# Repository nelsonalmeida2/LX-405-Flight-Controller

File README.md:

<div align="center">

# 🚁 LX-405 Flight Controller

<div align="center">
  
</div>

**A robust, Open Source FPV Flight Controller designed by a Computer Engineering student.**

</div>

---

## 🎯 Motivation & Philosophy

> *"In the modern era, Artificial Intelligence combined with human effort makes the impossible, inevitable."*

The **LX-405** project was born from a realization: as a Computer Engineering student entering the high-speed world of FPV, I found that too many flight controllers on the market suffer from electrical noise, weak regulators, and fragility under 6S voltage spikes.

My goal is to prove that **modern engineering is boundary-less**. Even though my degree is not strictly focused on electronics, the foundational skills acquired in my academic path—combined with a self-taught mindset and the leverage of **Large Language Models (LLMs)** as advanced design assistants—allow for the creation of professional-grade hardware.

This project demonstrates that with the right theoretical foundations and modern AI tools, it is possible to design a Flight Controller that is **more robust, cleaner, and potentially more cost-effective** at scale.

### 📐 Design Strategy: Modular & Hierarchical
Unlike typical hobbyist "flat" schematics, the LX-405 follows a strict **Hierarchical Design** approach.
Applying the software engineering principle of **Modularity** (Separation of Concerns), the hardware is divided into distinct hierarchical subsystems:
* **Power Management:** Encapsulates the voltage regulation logic (5V, 9V, 3.3V) with clean "Power Flags" logic.
* **MCU Core:** Contains the processor logic, clock, signaling, and boot configuration.
* **System Peripherals:** Groups active sensors (Gyro, Baro), OSD video processing logic, **Blackbox Logging**, and user feedback systems (LEDs/Buzzer).
* **Connectors IO:** Isolates physical interface definitions (plugs/pads) from logical connections to prevent routing conflicts.

### 🎓 Academic Foundations
This design applies core concepts from my Computer Engineering curriculum at **Universidade Lusófona**:
* **Digital Systems:** Logic gates and boolean algebra applied to circuit switching.
* **Computer Architecture:** Understanding CPU data paths, buses, registers, and instruction execution.
* **Advanced Computer Architectures:** Knowledge of processor constraints, memory hierarchy (cache), and hardware-software interaction.
* **Fundamentals of Physics:** Electromagnetism, electric fields, circuit analysis, and DC power dynamics.

---

## ⚡ Technical Specifications

### 🧠 Core System (Schematic Completed)
* **MCU:** STM32F405RGT6 (168MHz, 1MB Flash).
* **Clock:** 8MHz HSE Crystal Oscillator with 22pF load caps for precision timing.
* **Signal Integrity:** Dedicated LC Filter (Ferrite Bead + Caps) for **VDDA** analog noise suppression.
* **Safety:** Hardware-implemented Watchdog (NRST) and Bootloader (BOOT0) physical controls.

### 📡 Connectivity & Protocols
* **USB Interface:** Modern **USB-C** connector with dedicated ESD protection lines for firmware updates and Betaflight configuration.
* **Motor Protocols:**
    * 4x DSHOT Outputs (Timer-mapped for DMA collision avoidance).
    * **Redundant ESC Pads:** Parallel solder pads for motor signals, allowing field repairs if the main JST connector breaks.
* **Communication Ports:** 5x UARTs fully mapped for versatility:
    * **UART 1:** RC Link (ELRS / Crossfire).
    * **UART 2:** GPS / General Purpose.
    * **UART 3:** **Video Link** (SmartAudio for Analog **OR** MSP for DJI O3/HDZero).
    * **UART 4:** ESC Telemetry (Sensor Input).
    * **UART 6:** Peripheral Expansion (Bluetooth, Lidar, Secondary GPS).
    * *(Note: UART 5 was replaced by the High-Speed SDIO Bus).*
* **Video System (Hybrid):**
    * Dedicated **"Hybrid Power Pad"** offering both **5V** (Analog) and **9V** (High Power Digital) options for the VTX.
    * **Analog OSD:** **MAX7456** (or **AT7456E**) on SPI2 with dedicated video filtering.
* **Sensor Bus:** Dedicated SPI1 (High-Speed Gyro) and I2C1 (Barometer).

### 🛡️ On-Board Sensors & Peripherals
* **IMU (Gyroscope):** **BMI270** connected via Low-Noise **SPI1**.
    * Features hardware **EXTI Interrupt** (PC4) for ultra-low latency loop synchronization.
* **Barometer:** **DPS310** connected via **I2C1** for high-precision altitude hold.
* **Blackbox Logging:** **MicroSD Card Slot** via **4-bit SDIO** Interface.
    * Superior performance compared to SPI logging, enabling high-frequency data recording without CPU bottlenecks.
* **User Feedback:**
    * **Status LEDs:** Dedicated **LED_POWER** (Red) and **LED_STATUS** (Blue) for instant system diagnostics.
    * **Buzzer Driver:** Integrated active buzzer circuit for alarms and "turtle mode" feedback.

### 🔋 Power Plant (Tri-Rail Architecture)
A hierarchical power distribution system designed to minimize noise coupling and maximize versatility:

| Rail | Regulator | Specs | Application |
| :--- | :--- | :--- | :--- |
| **Input** | XT60 Direct | **3S-6S (10V - 25.2V)** | Wide-range input for Cinematic (6S) & Freestyle (4S) |
| **9V Rail** | TPS54302 | 3A Buck | **Hybrid Video Ready:** Supports DJI O3/Vista & Analog VTX |
| **5V Rail** | TPS54302 | 3A Buck | GPS, ELRS Receiver, Buzzer, OSD Chip |
| **3.3V Rail** | AP2112K | 500mA LDO | **Ultra-Low Noise** for MCU, Gyro, Baro & Blackbox |

---

## 📂 Repository Structure

```text
LX-405-Flight-Controller/
├── 📂 Hardware/          # KiCad Project Files (Schematics, PCB & Symbols)
├── 📂 Schematic/         # PDF Exports for easy viewing
├── 📂 Docs/              # Datasheets and Engineering Notes
├── 📄 LICENSE            # MIT License details
└── 📄 README.md          # Documentation
```
## 🛠 Development Roadmap

### Phase 1: Schematic Design 🔌

- [x] **Power Management**
    - [x] Input Stage: TVS protection and bulk capacitance (3S–6S filtering)
    - [x] 5V Regulator: Synchronous buck (TPS54302)
    - [x] 9V Regulator: High-current buck (TPS54302) for HD video
    - [x] 3.3V Regulator: Low-noise LDO (AP2112K) for sensors

- [x] **MCU Core**
    - [x] STM32F405RGT6: Symbol integration and pin definition
    - [x] Power decoupling & analog filtering (VDDA)
    - [x] Clock system: 8 MHz HSE crystal
    - [x] I/O architecture: Full UART / SPI / I2C mapping validation

- [x] **System Peripherals**
    - [x] Gyroscope (BMI270) via SPI1
    - [x] Barometer (DPS310) via I2C with address fix
    - [x] Blackbox: High-speed SDIO MicroSD slot implementation
    - [x] On-screen display (MAX7456 / AT7456E) via SPI2
    - [x] Visual / Audio: Status LEDs & buzzer circuit implemented

- [x] **Connectors & I/O**
    - [x] USB-C interface (data lines & ESD protection logic)
    - [x] ESC connector (standard pinout with telemetry)
    - [x] ESC redundancy: Parallel solder pads for emergency field repairs
    - [x] Hybrid VTX connector (selectable 5V / 9V)

- [x] **Design Validation**
    - [x] Electrical Rules Check (ERC): **PASSED with 0 errors**
    - [x] Schematic design finalized (**v0.6**)

### Phase 2: PCB Layout 📐

- [x] **Physical Implementation**
    - [x] Assign footprints (associating symbols with physical dimensions)
    - [x] Stackup definition (4-layer)
    - [x] Component placement (Optimized for noise reduction & assembly)
    - [x] Silkscreen & Labeling (User-friendly pin identification)
    - [ ] Routing (Traces & Ground Planes)
    - [ ] DRC (Design Rules Check) & Fabrication Output (Gerbers)

---

## 📜 License

This project is licensed under the **MIT License** — see the `LICENSE` file for details.

You are free to use, modify, and distribute this hardware design for private or commercial use, provided you include the original copyright notice.

As an **Open Source Hardware** project, contributions and forks are welcome.

---

<div align="center">

**Designed in Lisbon, Portugal 🇵🇹**  
Powered by Engineering Fundamentals & AI

</div>

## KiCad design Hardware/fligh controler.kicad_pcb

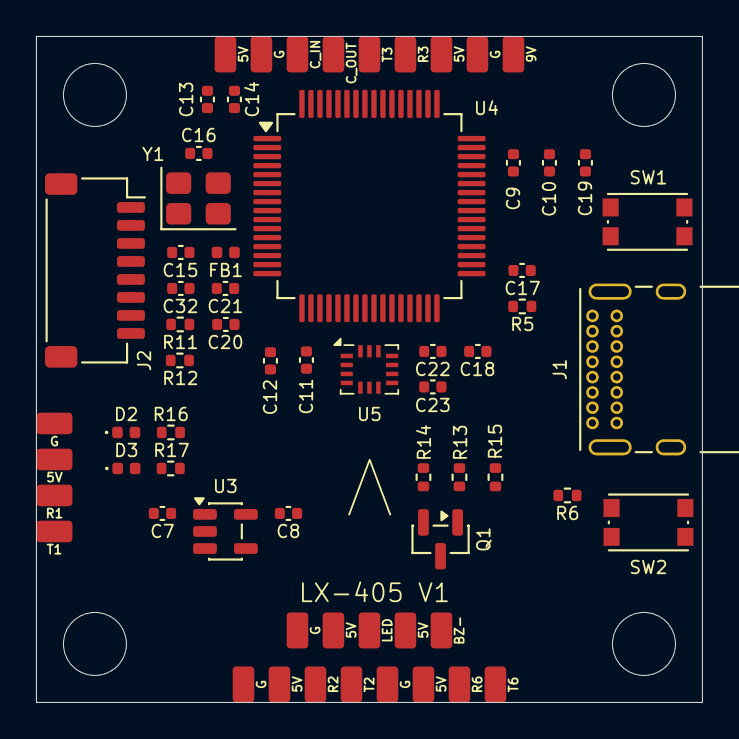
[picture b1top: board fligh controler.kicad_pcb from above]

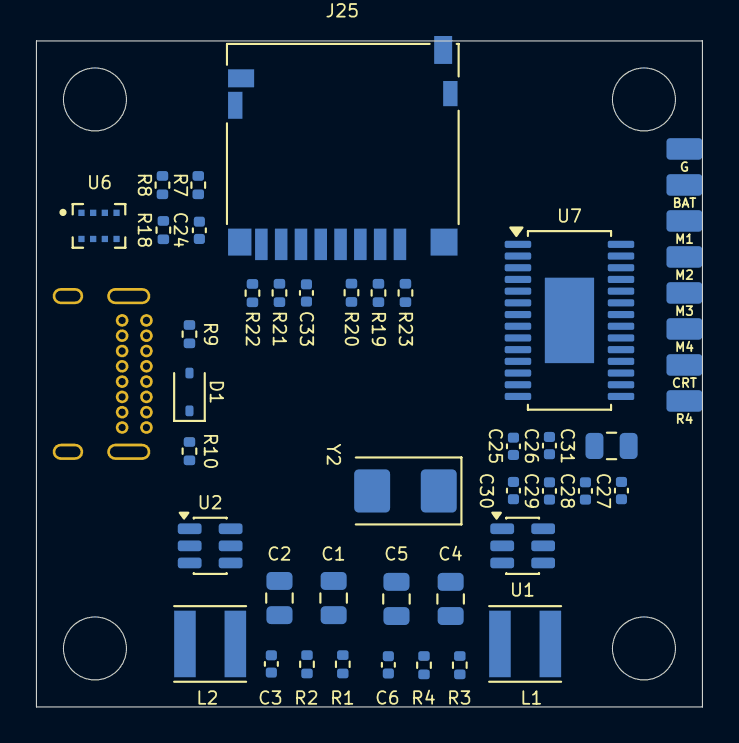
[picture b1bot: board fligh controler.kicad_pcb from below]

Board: 2 copper layers, 37.0 x 37.0 mm, 111 parts (46 on the bottom side), 70 nets, no tracks yet.

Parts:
5V, 5V#2, 5V#3, 5V#4, 5V#5, 5V#6, 5V#7: +5V; Pad_TestPoint_Retangular
9V: +9V; Pad_TestPoint_Retangular
BAT: BAT+; Pad_TestPoint_Retangular
BZ-: BUZZER-; Pad_TestPoint_Retangular
C1, C4: 10uF 50V; C_0805_2012Metric
C2: 22uF 25V; C_0805_2012Metric
C3, C6: 0.1uF 50V; C_0402_1005Metric
C5: 22uF 10V; C_0805_2012Metric
C7, C8, C21: 1uF 16V; C_0402_1005Metric
C9, C10, C11, C12, C13, C17, C20, C22, C23, C24, C25, C26, C27, C30, C32, C33: 100nF 16V; C_0402_1005Metric
C14, C18, C19: 4.7uF 16V; C_0402_1005Metric
C15, C16, C28, C29: 22pF 16V; C_0402_1005Metric
C31: 47uF 16V; C_0805_2012Metric
CRT: CURRENT_SENSE; Pad_TestPoint_Retangular
C_IN: CAM_VIDEO_IN; Pad_TestPoint_Retangular
C_OUT: VTX_VIDEO_OUT; Pad_TestPoint_Retangular
D1: D_Schottky; D_SOD-323
D2: Red; LED_0402_1005Metric
D3: Blue; LED_0402_1005Metric
FB1: 100R @ 100MHz; L_0402_1005Metric
G: GND; Pad_TestPoint_Retangular
G#2, G#3, G#4, G#5, G#6, G#7: GND; Pad_TestPoint_Retangular
J1: USB_C_Receptacle_USB2.0_16P; USB_C_Receptacle_GCT_USB4085
J2: Conn_01x08; JST_SH_SM08B-SRSS-TB_1x08-1MP_P1.00mm_Horizontal
J25: Micro_SD_Card; microSD_HC_Hirose_DM3D-SF
L1, L2: 10uH 3A; L_Taiyo-Yuden_NR-40xx
LED: LED_STRIP; Pad_TestPoint_Retangular
M1: MOTOR_1; Pad_TestPoint_Retangular
M2: MOTOR_2; Pad_TestPoint_Retangular
M3: MOTOR_3; Pad_TestPoint_Retangular
M4: MOTOR_4; Pad_TestPoint_Retangular
Q1: 2N7002; SOT-23
R1: RX1; Pad_TestPoint_Retangular
R1#2, R3#2: 100k 1%; R_0402_1005Metric
R2: RX2; Pad_TestPoint_Retangular
R2#2: 7.15k 1%; R_0402_1005Metric
R3: RX3; Pad_TestPoint_Retangular
R4: RX4; Pad_TestPoint_Retangular
R4#2: 13.7k 1%; R_0402_1005Metric
R5, R6, R11, R14: 10k; R_0402_1005Metric
R6#2: RX6; Pad_TestPoint_Retangular
R7, R8, R18: 4.7k; R_0402_1005Metric
R9, R10: 5.1k; R_0402_1005Metric
R12, R13, R16: 1k; R_0402_1005Metric
R15, R17: 330Ω; R_0402_1005Metric
R19, R20, R21, R22, R23: 47k; R_0402_1005Metric
SW1, SW2: SW_Push; SW_Push_1P1T_NO_CK_KMR2
T1: TX1; Pad_TestPoint_Retangular
T2: TX2; Pad_TestPoint_Retangular
T3: TX3; Pad_TestPoint_Retangular
T6: TX6; Pad_TestPoint_Retangular
U1, U2: TPS54302; SOT-23-6
U3: AP2112K-3.3; SOT-23-5
U4: STM32F405RGT6; LQFP-64_10x10mm_P0.5mm
U5: BMI270; Bosch_LGA-14_3x2.5mm_P0.5mm
U6: DPS310
U7: MAX7456EUI_T; TSSOP-28-1EP_4.4x9.7mm_P0.65mm_EP2.74x4.75mm
Y1: Crystal_GND24; Crystal_SMD_3225-4Pin_3.2x2.5mm
Y2: Crystal; Crystal_SMD_5032-2Pin_5.0x3.2mm

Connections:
+3V3: C8.2, C9.1, C10.1, C11.1, C12.1, C13.1, C14.1, C22.2, C23.2, C24.1, FB1.2, J25.4 (VDD), R5.1, R7.1, R8.2, R16.1, R19.1, R20.1, R21.1, R22.1, R23.1, SW2.2, U3.5 (VOUT), U4.1 (VBAT), U4.19 (VDD), U4.32 (VDD), U4.48 (VDD), U4.64 (VDD), U5.5 (VDDIO), U5.8 (VDD), U6.2 (~CSB), U6.6 (VDDIO), U6.8 (VDD)
+5V: 5V.1, 5V#2.1, 5V#3.1, 5V#4.1, 5V#5.1, 5V#6.1, 5V#7.1, C5.2, C7.2, C25.1, C26.1, C27.1, D1.1 (K), L2.1, R3#2.2, U3.1 (VIN), U3.3 (EN), U7.3 (DVDD), U7.19 (~RESET), U7.21 (AVDD), U7.24 (PVDD)
+9V: 9V.1, C2.2, L1.1, R1#2.2
/Connectors_IO/BUZZER-: BZ-.1, Q1.3 (D)
/Connectors_IO/CAM_VIDEO_IN: C30.2, C_IN.1
/Connectors_IO/CURRENT_SENSE: CRT.1, J2.7, U4.9 (PC1)
/Connectors_IO/LED_STRIP: R15.1, U4.14 (PA0)
/Connectors_IO/MOTOR_1: J2.3, M1.1, U4.26 (PB0)
/Connectors_IO/MOTOR_2: J2.4, M2.1, U4.27 (PB1)
/Connectors_IO/MOTOR_3: J2.5, M3.1, U4.56 (PB4)
/Connectors_IO/MOTOR_4: J2.6, M4.1, U4.57 (PB5)
/Connectors_IO/RX1: R1.1, U4.42 (PA9)
/Connectors_IO/RX2: R2.1, U4.16 (PA2)
/Connectors_IO/RX3: R3.1, U4.29 (PB10)
/Connectors_IO/RX4: J2.8, R4.1, U4.15 (PA1)
/Connectors_IO/RX6: R6#2.1, U4.37 (PC6)
/Connectors_IO/TX1: T1.1, U4.43 (PA10)
/Connectors_IO/TX2: T2.1, U4.17 (PA3)
/Connectors_IO/TX3: T3.1, U4.30 (PB11)
/Connectors_IO/TX6: T6.1, U4.38 (PC7)
/Connectors_IO/USB_DM: J1.A7 (D-), J1.B7 (D-), U4.44 (PA11)
/Connectors_IO/USB_DP: J1.A6 (D+), J1.B6 (D+), U4.45 (PA12)
/Connectors_IO/VTX_VIDEO_OUT: C31.2, C_OUT.1
/MCU_Core/BUZZER_CTRL: R13.2, U4.2 (PC13)
/MCU_Core/GYRO_CS: U4.20 (PA4), U5.12 (CSB)
/MCU_Core/GYRO_EXTI: U4.24 (PC4), U5.4 (INT1)
/MCU_Core/I2C1_SCL: R8.1, U4.58 (PB6), U6.4 (SCK)
/MCU_Core/I2C1_SDA: R7.2, U4.59 (PB7), U6.3 (SDI)
/MCU_Core/LED_STATUS: R17.1, U4.25 (PC5)
/MCU_Core/OSD_CS: U4.33 (PB12), U7.8 (~CS)
/MCU_Core/SDIO_CK: J25.5 (CLK), U4.53 (PC12)
/MCU_Core/SDIO_CMD: J25.3 (CMD), R20.2, U4.54 (PD2)
/MCU_Core/SDIO_D0: J25.7 (DAT0), R21.2, U4.39 (PC8)
/MCU_Core/SDIO_D1: J25.8 (DAT1), R22.2, U4.40 (PC9)
/MCU_Core/SDIO_D2: J25.1 (DAT2), R23.2, U4.51 (PC10)
/MCU_Core/SDIO_D3: J25.2 (DAT3/CD), R19.2, U4.52 (PC11)
/MCU_Core/SPI1_MISO: U4.23 (PA7), U5.1 (SDO)
/MCU_Core/SPI1_MOSI: U4.22 (PA6), U5.14 (SDX)
/MCU_Core/SPI1_SCK: U4.21 (PA5), U5.13 (SCX)
/MCU_Core/SPI2_MISO: U4.35 (PB14), U7.11 (SDOUT)
/MCU_Core/SPI2_MOSI: U4.36 (PB15), U7.9 (SDIN)
/MCU_Core/SPI2_SCK: U4.34 (PB13), U7.10 (SCLK)
/MCU_Core/VBAT_SENSE: C32.2, R11.1, R12.2, U4.8 (PC0)
BAT+: BAT.1, C1.1, C4.1, J2.2, R11.2, U1.3 (VIN), U1.5 (EN), U2.3 (VIN), U2.5 (EN)
GND: C1.2, C2.1, C4.2, C5.1, C7.1, C8.1, C9.2, C10.2, C11.2, C12.2, C13.2, C14.2, C15.1, C16.1, C17.1, C18.1, C19.1, C20.1, C21.1, C22.1, C23.1, C24.2, C25.2, C26.2, C27.2, C28.2, C29.2, C32.1, C33.1, C33.2, D2.1 (K), D3.1 (K), G.1, G#2.1, G#3.1, G#4.1, G#5.1, G#6.1, G#7.1, J1.A1 (GND), J1.A12 (GND), J1.B1 (GND), J1.B12 (GND), J1.S1 (SHIELD), J2.1, J25.6 (VSS), J25.9 (SHIELD), Q1.2 (S), R2#2.1, R4#2.1, R6.1, R9.2, R10.2, R12.1, R14.1, R18.2, SW1.1, U1.1 (GND), U2.1 (GND), U3.2 (GND), U4.12 (VSSA), U4.18 (VSS), U4.63 (VSS), U5.6 (GNDIO), U5.7 (GND), U6.1 (GND), U6.7 (GND), U7.4 (DGND), U7.20 (AGND), U7.23 (PGND), U7.29 (EP), Y1.2 (G), Y1.4 (G)
unnamed: D1.2 (A), J1.A4 (VBUS), J1.A9 (VBUS), J1.B4 (VBUS), J1.B9 (VBUS)
unnamed: D2.2 (A), R16.2
unnamed: D3.2 (A), R17.2
unnamed: J1.A5 (CC1), R9.1
unnamed: J1.B5 (CC2), R10.1
unnamed: LED.1, R15.2
unnamed: Q1.1 (G), R13.1, R14.2
unnamed: C3.2, L1.2, U1.6 (BOOT)
unnamed: R1#2.1, R2#2.2, U1.4 (FB)
unnamed: C3.1, U1.2 (SW)
unnamed: C6.2, L2.2, U2.6 (BOOT)
unnamed: R3#2.1, R4#2.2, U2.4 (FB)
unnamed: C6.1, U2.2 (SW)
unnamed: R6.2, SW2.1, U4.60 (BOOT0)
unnamed: C17.2, R5.2, SW1.2, U4.7 (NRST)
unnamed: C15.2, U4.5 (PH0), Y1.1
unnamed: C16.2, U4.6 (PH1), Y1.3
unnamed: C18.2, U4.31 (VCAP_1)
unnamed: C19.2, U4.47 (VCAP_2)
unnamed: C20.2, C21.2, FB1.1, U4.13 (VDDA)
unnamed: R18.1, U6.5 (SDO)
unnamed: C28.1, U7.5 (CLKIN), Y2.2
unnamed: C30.1, U7.22 (VIN)
unnamed: C31.1, U7.26 (VOUT)
unnamed: C29.1, U7.6 (XFB), Y2.1

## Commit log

2026-01-16 Initial Commit: Project structure, README, and Power Management module
2026-01-17 feat(mcu): finalize core schematic and update project documentation
    - MCU_Core: Completed pin definitions and Hierarchical Labels (SPI, UART, I2C, Motors).
    - Root: Updated sheet pins to reflect the new MCU architecture.
    - Docs: Refined README.md with detailed hierarchical roadmap and MIT License.
    - Docs: Added 'Connectors & I/O' breakdown to the development plan.
2026-01-17 feat: implement system peripherals (OSD, Gyro, Baro)
2026-01-18 Finalize schematic: Add connectors, LEDs, Buzzer and fix all ERC errors
2026-01-18 Update schematic: Add SDIO Blackbox, ESC Redundancy and remove UART5
2026-01-27 Finalize component placement and silkscreen
